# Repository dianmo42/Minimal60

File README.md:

# Minimal60: A 60% customized keyboard with separated spacebar

This keyboard is inspired by Neson Design Keyboards, and GMK keycaps "Minimal".

## Case

The original [step file](./case/Minimal60.step) comes with no decoration. Please, feel free to make your own modification. You may find some useful resources [here](./resources/).

## PCB 

The PCB uses Atmega32u4 and FPC connector. You can find the UDB with FPC connector in my another repository: [UDB-C-FPC](https://github.com/dianmo42/UDB-C-FPC).

## Firmware

Unfortunately, I haven't got time to learn to write the QMK firmware : (

Please let me know if you could offer some help : )

## Attention!

The feasibility of this project is not guaranteed. Please conduct sample testing before proceeding to formal production.

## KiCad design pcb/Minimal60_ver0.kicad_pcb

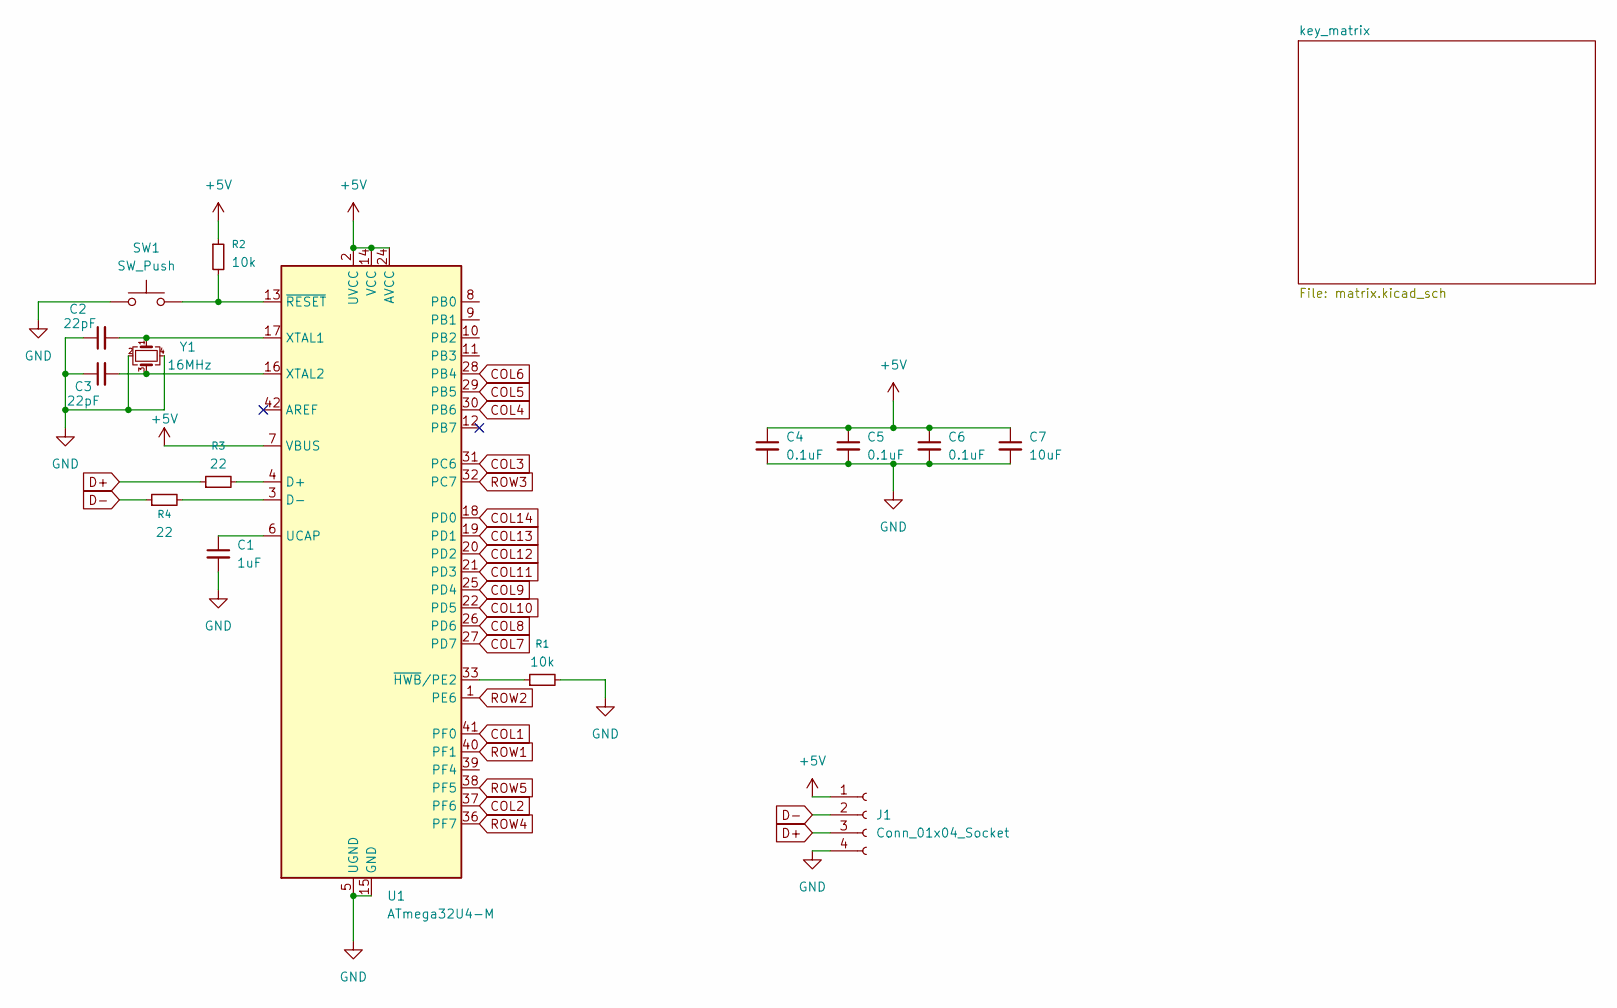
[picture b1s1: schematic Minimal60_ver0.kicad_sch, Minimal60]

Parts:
C1: 1uF; C_0805_2012Metric
C2, C3: 22pF; C_0805_2012Metric
C4, C5, C6: 0.1uF; C_0805_2012Metric
C7: 10uF; C_0805_2012Metric
J1: Conn_01x04_Socket; Amphenol_F32Q-1A7x1-11004_1x04-1MP_P0.5mm_Horizontal
R1, R2: 10k; R_0805_2012Metric
R3, R4: 22; R_0805_2012Metric
SW1: SW_Push; SW_SPST_SKQG_WithoutStem
U1: ATmega32U4-M; QFN-44-1EP_7x7mm_P0.5mm_EP5.2x5.2mm
Y1: 16MHz; Crystal_SMD_3225-4Pin_3.2x2.5mm

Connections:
+5V: C4.1, C5.1, C6.1, C7.1, J1.1, R2.1, U1.2 (UVCC), U1.7 (VBUS), U1.14 (VCC), U1.24 (AVCC), U1.34 (VCC), U1.44 (AVCC)
COL1: U1.41 (PF0); also elsewhere on the board
COL2: U1.37 (PF6); also elsewhere on the board
COL3: U1.31 (PC6); also elsewhere on the board
COL4: U1.30 (PB6); also elsewhere on the board
COL5: U1.29 (PB5); also elsewhere on the board
COL6: U1.28 (PB4); also elsewhere on the board
COL7: U1.27 (PD7); also elsewhere on the board
COL8: U1.26 (PD6); also elsewhere on the board
COL9: U1.25 (PD4); also elsewhere on the board
COL10: U1.22 (PD5); also elsewhere on the board
COL11: U1.21 (PD3); also elsewhere on the board
COL12: U1.20 (PD2); also elsewhere on the board
COL13: U1.19 (PD1); also elsewhere on the board
COL14: U1.18 (PD0); also elsewhere on the board
D+: J1.3, R3.1
D-: J1.2, R4.1
GND: C1.2, C2.1, C3.1, C4.2, C5.2, C6.2, C7.2, J1.4, J1.MP, R1.2, SW1.1, U1.5 (UGND), U1.15 (GND), U1.23 (GND), U1.35 (GND), U1.43 (GND), U1.45 (GND), Y1.2, Y1.4
unnamed: R3.2, U1.4 (D+)
unnamed: R4.2, U1.3 (D-)
unnamed: C1.1, U1.6 (UCAP)
unnamed: C2.2, U1.17 (XTAL1), Y1.1
unnamed: C3.2, U1.16 (XTAL2), Y1.3
unnamed: R1.1, U1.33 (~HWB/PE2)
unnamed: R2.2, SW1.2, U1.13 (~RESET)
ROW1: U1.40 (PF1); also elsewhere on the board
ROW2: U1.1 (PE6); also elsewhere on the board
ROW3: U1.32 (PC7); also elsewhere on the board
ROW4: U1.36 (PF7); also elsewhere on the board
ROW5: U1.38 (PF5); also elsewhere on the board

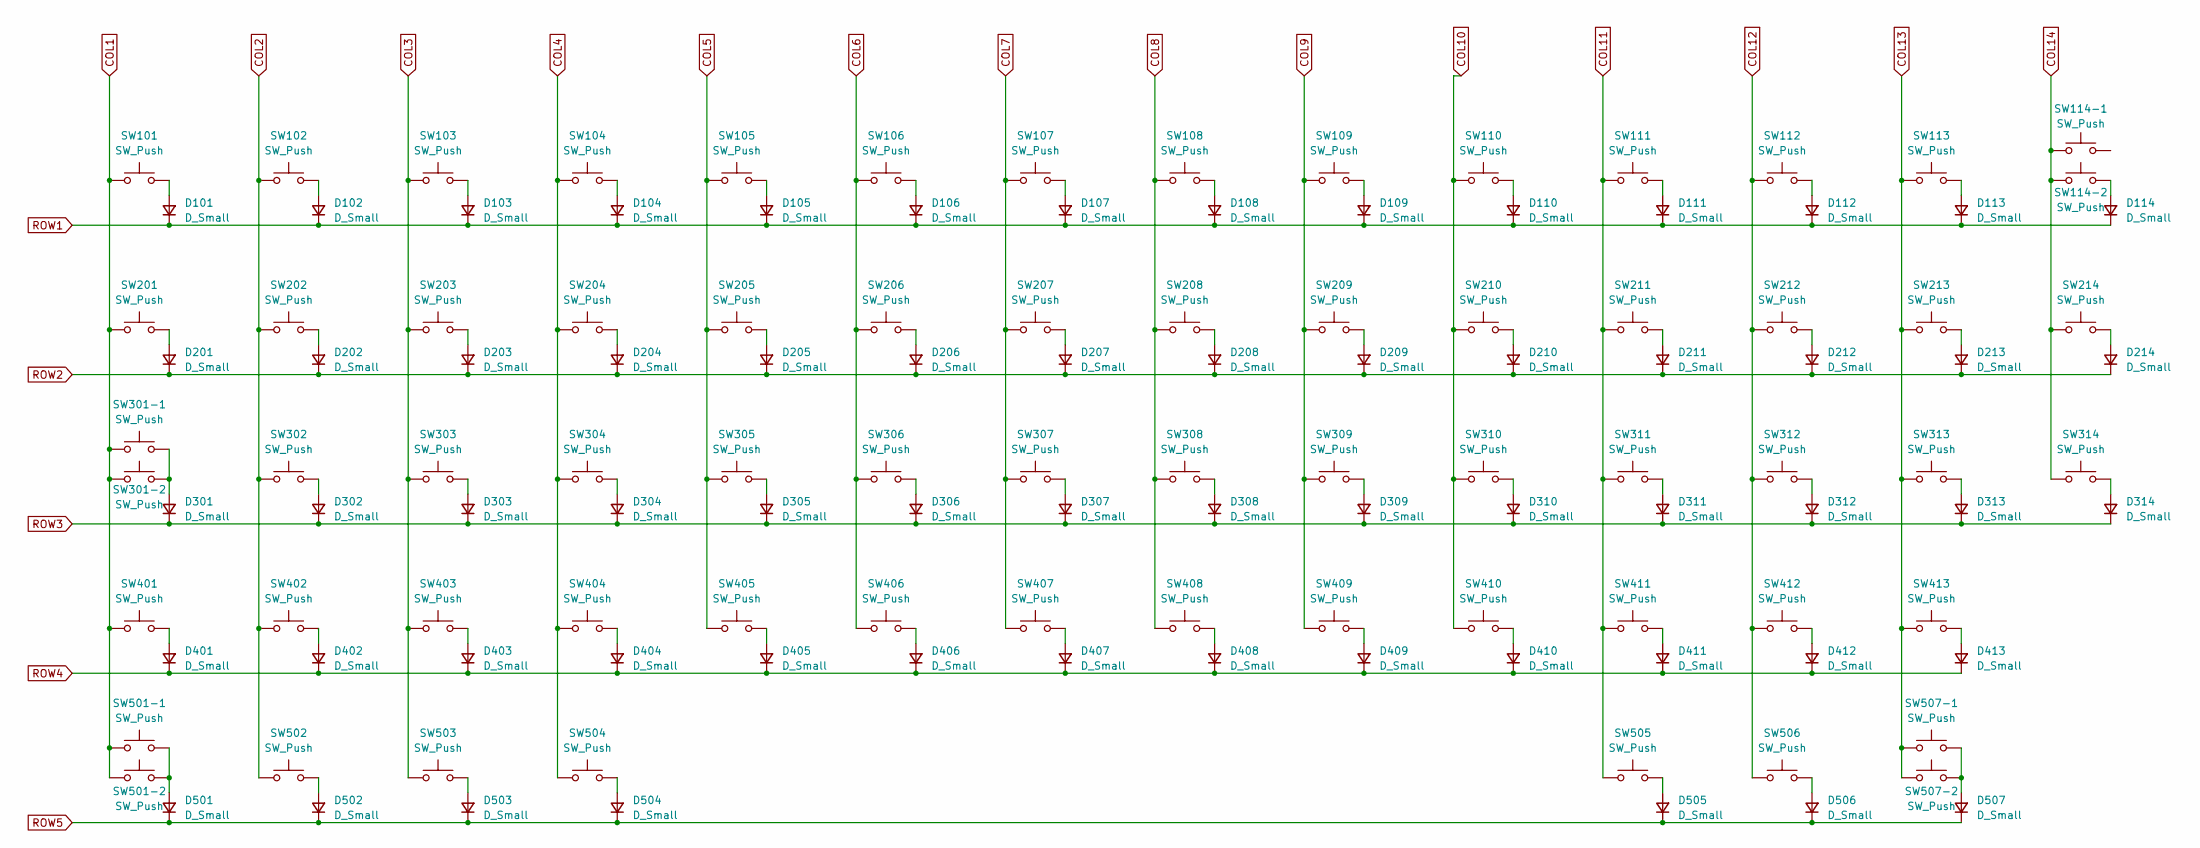
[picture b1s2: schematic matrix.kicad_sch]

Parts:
D101, D102, D103, D104, D105, D106, D107, D108, D109, D110, D111, D112, D113, D114, D201, D202, D203, D204, D205, D206, D207, D208, D209, D210, D211, D212, D213, D214, D301, D302, D303, D304, D305, D306, D307, D308, D309, D310, D311, D312, D313, D314, D401, D402, D403, D404, D405, D406, D407, D408, D409, D410, D411, D412, D413, D501, D502, D503, D504, D505, D506, D507: D_Small; D_SOD-123
SW101, SW102, SW103, SW104, SW105, SW106, SW107, SW108, SW109, SW110, SW111, SW112, SW113, SW114-1, SW202, SW203, SW204, SW205, SW206, SW207, SW208, SW209, SW210, SW211, SW212, SW213, SW302, SW303, SW304, SW305, SW306, SW307, SW308, SW309, SW310, SW311, SW312, SW314, SW402, SW403, SW404, SW405, SW406, SW407, SW408, SW409, SW410, SW411, SW413, SW502, SW506: SW_Push; MX-Solderable-1U
SW114-2: SW_Push; MX-Solderable-2U
SW201, SW214, SW501-2, SW503, SW505, SW507-1: SW_Push; MX-Solderable-1.5U
SW301-1, SW501-1, SW507-2: SW_Push; MX-Solderable-1.25U
SW301-2, SW412: SW_Push; MX-Solderable-1.75U
SW313, SW401: SW_Push; MX-Solderable-2.25U
SW504: SW_Push; MX-Solderable-7U-ReversedStabilizers

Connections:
COL1: SW101.1, SW201.1, SW301-1.1, SW301-2.1, SW401.1, SW501-1.1, SW501-2.1; also elsewhere on the board
COL2: SW102.1, SW202.1, SW302.1, SW402.1, SW502.1; also elsewhere on the board
COL3: SW103.1, SW203.1, SW303.1, SW403.1, SW503.1; also elsewhere on the board
COL4: SW104.1, SW204.1, SW304.1, SW404.1, SW504.1; also elsewhere on the board
COL5: SW105.1, SW205.1, SW305.1, SW405.1; also elsewhere on the board
COL6: SW106.1, SW206.1, SW306.1, SW406.1; also elsewhere on the board
COL7: SW107.1, SW207.1, SW307.1, SW407.1; also elsewhere on the board
COL8: SW108.1, SW208.1, SW308.1, SW408.1; also elsewhere on the board
COL9: SW109.1, SW209.1, SW309.1, SW409.1; also elsewhere on the board
COL10: SW110.1, SW210.1, SW310.1, SW410.1; also elsewhere on the board
COL11: SW111.1, SW211.1, SW311.1, SW411.1, SW505.1; also elsewhere on the board
COL12: SW112.1, SW212.1, SW312.1, SW412.1, SW506.1; also elsewhere on the board
COL13: SW113.1, SW213.1, SW313.1, SW413.1, SW507-1.1, SW507-2.1; also elsewhere on the board
COL14: SW114-1.1, SW114-2.1, SW214.1, SW314.1; also elsewhere on the board
unnamed: D101.2 (A), SW101.2
unnamed: D102.2 (A), SW102.2
unnamed: D103.2 (A), SW103.2
unnamed: D104.2 (A), SW104.2
unnamed: D105.2 (A), SW105.2
unnamed: D106.2 (A), SW106.2
unnamed: D107.2 (A), SW107.2
unnamed: D108.2 (A), SW108.2
unnamed: D109.2 (A), SW109.2
unnamed: D110.2 (A), SW110.2
unnamed: D111.2 (A), SW111.2
unnamed: D112.2 (A), SW112.2
unnamed: D113.2 (A), SW113.2
unnamed: D114.2 (A), SW114-2.2
unnamed: D201.2 (A), SW201.2
unnamed: D202.2 (A), SW202.2
unnamed: D203.2 (A), SW203.2
unnamed: D204.2 (A), SW204.2
unnamed: D205.2 (A), SW205.2
unnamed: D206.2 (A), SW206.2
unnamed: D207.2 (A), SW207.2
unnamed: D208.2 (A), SW208.2
unnamed: D209.2 (A), SW209.2
unnamed: D210.2 (A), SW210.2
unnamed: D211.2 (A), SW211.2
unnamed: D212.2 (A), SW212.2
unnamed: D213.2 (A), SW213.2
unnamed: D214.2 (A), SW214.2
unnamed: D301.2 (A), SW301-1.2, SW301-2.2
unnamed: D302.2 (A), SW302.2
unnamed: D303.2 (A), SW303.2
unnamed: D304.2 (A), SW304.2
unnamed: D305.2 (A), SW305.2
unnamed: D306.2 (A), SW306.2
unnamed: D307.2 (A), SW307.2
unnamed: D308.2 (A), SW308.2
unnamed: D309.2 (A), SW309.2
unnamed: D310.2 (A), SW310.2
unnamed: D311.2 (A), SW311.2
unnamed: D312.2 (A), SW312.2
unnamed: D313.2 (A), SW313.2
unnamed: D314.2 (A), SW314.2
unnamed: D401.2 (A), SW401.2
unnamed: D402.2 (A), SW402.2
unnamed: D403.2 (A), SW403.2
unnamed: D404.2 (A), SW404.2
unnamed: D405.2 (A), SW405.2
unnamed: D406.2 (A), SW406.2
unnamed: D407.2 (A), SW407.2
unnamed: D408.2 (A), SW408.2
unnamed: D409.2 (A), SW409.2
unnamed: D410.2 (A), SW410.2
unnamed: D411.2 (A), SW411.2
unnamed: D412.2 (A), SW412.2
unnamed: D413.2 (A), SW413.2
unnamed: D501.2 (A), SW501-1.2, SW501-2.2
unnamed: D502.2 (A), SW502.2
unnamed: D503.2 (A), SW503.2
unnamed: D504.2 (A), SW504.2
unnamed: D505.2 (A), SW505.2
unnamed: D506.2 (A), SW506.2
unnamed: D507.2 (A), SW507-1.2, SW507-2.2
ROW1: D101.1 (K), D102.1 (K), D103.1 (K), D104.1 (K), D105.1 (K), D106.1 (K), D107.1 (K), D108.1 (K), D109.1 (K), D110.1 (K), D111.1 (K), D112.1 (K), D113.1 (K), D114.1 (K); also elsewhere on the board
ROW2: D201.1 (K), D202.1 (K), D203.1 (K), D204.1 (K), D205.1 (K), D206.1 (K), D207.1 (K), D208.1 (K), D209.1 (K), D210.1 (K), D211.1 (K), D212.1 (K), D213.1 (K), D214.1 (K); also elsewhere on the board
ROW3: D301.1 (K), D302.1 (K), D303.1 (K), D304.1 (K), D305.1 (K), D306.1 (K), D307.1 (K), D308.1 (K), D309.1 (K), D310.1 (K), D311.1 (K), D312.1 (K), D313.1 (K), D314.1 (K); also elsewhere on the board
ROW4: D401.1 (K), D402.1 (K), D403.1 (K), D404.1 (K), D405.1 (K), D406.1 (K), D407.1 (K), D408.1 (K), D409.1 (K), D410.1 (K), D411.1 (K), D412.1 (K), D413.1 (K); also elsewhere on the board
ROW5: D501.1 (K), D502.1 (K), D503.1 (K), D504.1 (K), D505.1 (K), D506.1 (K), D507.1 (K); also elsewhere on the board

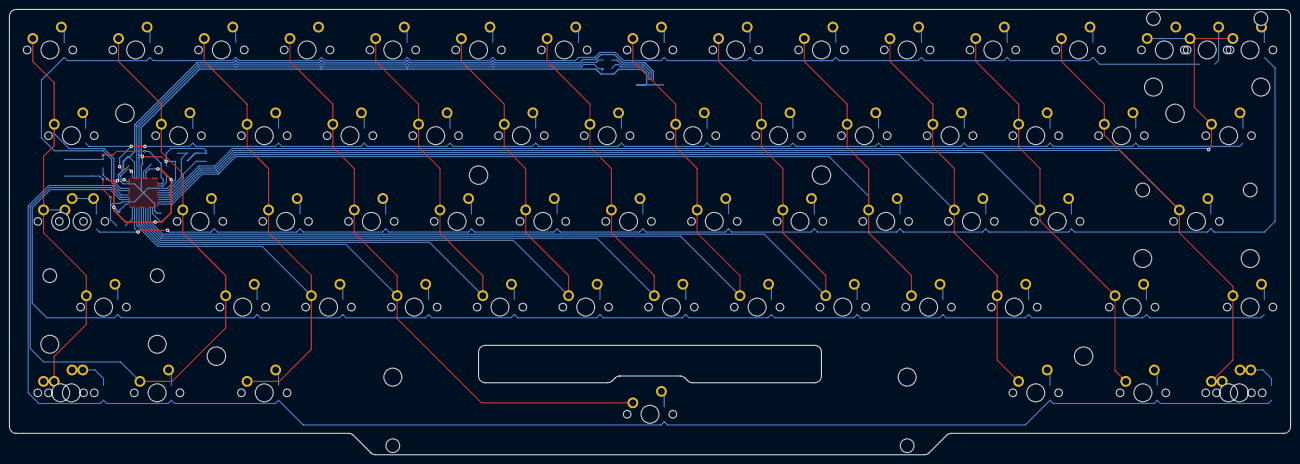
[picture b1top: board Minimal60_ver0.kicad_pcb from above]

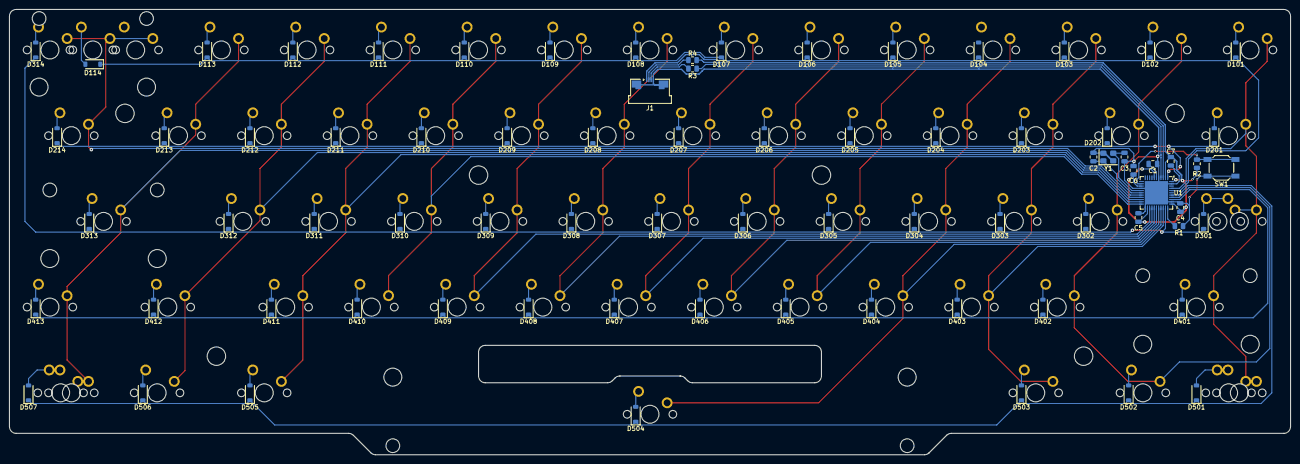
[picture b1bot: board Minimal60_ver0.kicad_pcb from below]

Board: 2 copper layers, 284.7 x 99.0 mm, 143 parts (77 on the bottom side), 92 nets.

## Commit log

2024-10-05 update: version1
2024-10-05 update: README
2024-10-05 update: modify space cut
2024-10-05 update: modify space cutout
2024-10-05 udpate: modify space cutoff
2024-10-06 keep only one plate dxf file
2024-10-06 move to production
2024-10-06 readme
2025-09-04 Minimal60 ver1
2025-09-04 License
